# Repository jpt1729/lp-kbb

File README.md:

# Low-profile Keyboard

This is a low profile 65% keyboard with a rotary encoder (for volume + mute/unmute). This project uses Gateron's ks33 switches and their respective hotswap sockets. This is all on top of a skeletal 3d printed case. (also texas themed)

I made this project because 1 I just want a custom keyboard and 2 the keyboard I want kinda doesn't exist. I don't haven't really seen these keyboard with the skeletal cases or chamfered edges so I kinda wanted to make it + its texas themed :).

# Photos

# BOM
| Item | Quantity Used | Quantity Purchased | Designator | Part Number / Description | Link | Cost |
|------|---------------|--------------------|------------|----------------------------|------|------|
| Gateron Grey Heron LP Switches | 70 | 2 (35-pack) | SW1–SW70 | Gateron Low‑Profile Grey Heron | [Gateron](https://www.gateron.com/products/gateron-low-profile-grey-heron-switch?VariantsId=10866) | $30.10 |
| Gateron Sky Plate-Mounted Stabilizer | 1 | 1 | STAB1 | Gateron Low‑Profile Stabilizer | [Gateron](https://www.gateron.com/products/gateron-low-profile-sky-plate-mounted-stabilizer) | $10.00 |
| Gateron Hot‑Swap PCB Socket | 1 | 1 | S1 | LP Hotswap Socket | [Gateron](https://www.gateron.com/products/gateron-low-profile-switch-hot-swap-pcb-socket?VariantsId=10233) | $7.00 |
| Low profile keycaps | 1 | 1 | | Keycaps | [kbdcraft](https://kbdcraft.store/products/keycap-lp) | $20.35 |
| EC11 | 1 | 1 | EC11 | EC11 Encoder |  | *Owned* |
| 1N4148 Diodes | 1 | 1 | D | Keyboard Diodes | [AliExpress](https://www.aliexpress.us/item/2255799955957794.html) | $1.48 |
| Heatset inserts| 1 | 1 |  | | [AliExpress](https://www.aliexpress.us/item/3256807534424119.html) | $2.71 |
| Orpheus Pico | 1 | 1 | U1 | RP2040 Custom Module |  | *Owned* |
| EC11 Encoder | 1 | 1 | ENC2 | EC11 (Spare) |  | *Owned* |
| Headers | 1 | 1 | | 2.54mm Male/Female Headers | [AliExpress](https://www.aliexpress.us/item/2255800687544049.html) | $1.99 |
| PCB (w/o discount) + shipping | 1 | 5 |  | JLCPCB |  | $30.76 |
| Case | 1 | 1 |  | 3d printed case |  | |
| Shipping Gateron (+ Gateron service fee) |  |  |  | Shipping from Gateron |  | $11.23 |
| Shipping AliExpress |  |  |  | Shipping from AliExpress |  | $3.00 |
| **Total** |  |  |  | | | **$118.62** |

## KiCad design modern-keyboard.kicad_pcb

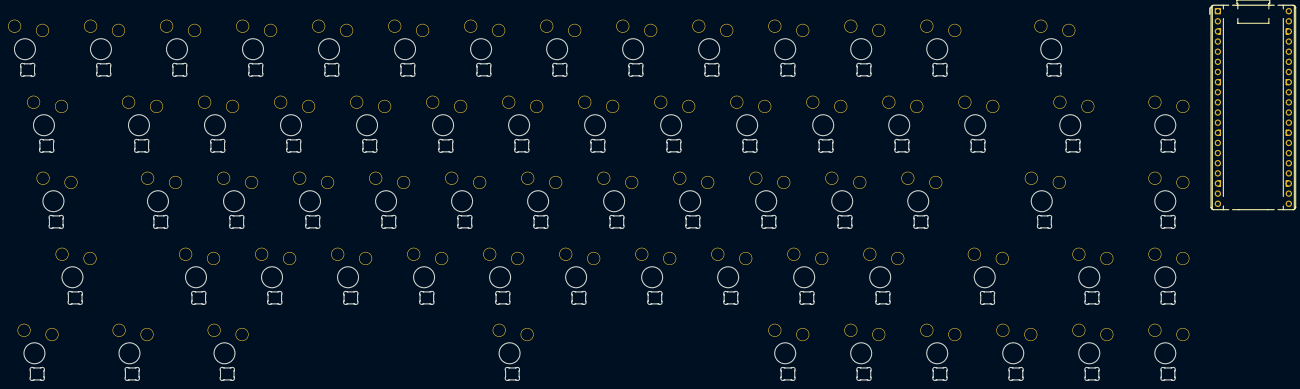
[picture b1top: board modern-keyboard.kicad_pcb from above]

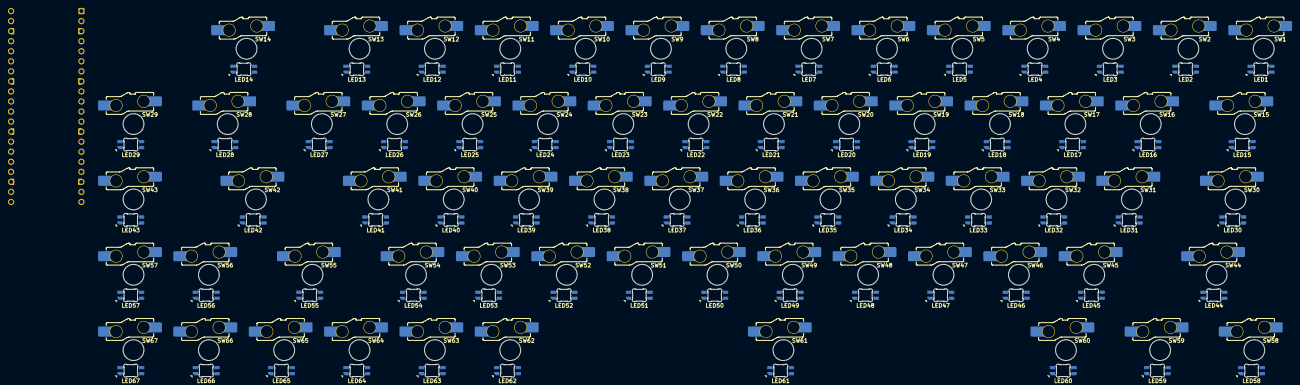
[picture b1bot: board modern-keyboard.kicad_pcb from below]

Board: 2 copper layers, 135 parts (134 on the bottom side), 84 nets, no tracks yet.

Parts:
A1: RaspberryPi_Pico; RaspberryPi_Pico_Common_THT
LED1, LED2, LED3, LED4, LED5, LED6, LED7, LED8, LED9, LED10, LED11, LED12, LED13, LED14, LED15, LED16, LED17, LED18, LED19, LED20, LED21, LED22, LED23, LED24, LED25, LED26, LED27, LED28, LED29, LED30, LED31, LED32, LED33, LED34, LED35, LED36, LED37, LED38, LED39, LED40, LED41, LED42, LED43, LED44, LED45, LED46, LED47, LED48, LED49, LED50, LED51, LED52, LED53, LED54, LED55, LED56, LED57, LED58, LED59, LED60, LED61, LED62, LED63, LED64, LED65, LED66, LED67: SK6812MINI-E; LED_KS33_6028R
SW1, SW2, SW3, SW4, SW5, SW6, SW7, SW8, SW9, SW10, SW11, SW12, SW13, SW16, SW17, SW18, SW19, SW20, SW21, SW22, SW23, SW24, SW25, SW26, SW27, SW29, SW31, SW32, SW33, SW34, SW35, SW36, SW37, SW38, SW39, SW40, SW41, SW43, SW45, SW46, SW47, SW48, SW49, SW50, SW51, SW52, SW53, SW54, SW56, SW57, SW62, SW63, SW64, SW65, SW66, SW67: SW_Push_45deg; SW_KS33_HS_KS-2P02B01-02_HS_1u
SW14: SW_Push_45deg; SW_KS33_HS_KS-2P02B01-02_HS_2u
SW15, SW28: SW_Push_45deg; SW_KS33_HS_KS-2P02B01-02_1.5u
SW30, SW55: SW_Push_45deg; SW_KS33_HS_KS-2P02B01-02_1.75u
SW42, SW44: SW_Push_45deg; SW_KS33_HS_KS-2P02B01-02_HS_2.25u
SW58, SW59, SW60: SW_Push_45deg; SW_KS33_HS_KS-2P02B01-02_1.25u
SW61: SW_Push_45deg; SW_KS33_HS_KS-2P02B01-02_HS_6.25u

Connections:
+5V: A1.40 (VBUS), LED1.1 (VDD), LED2.1 (VDD), LED3.1 (VDD), LED4.1 (VDD), LED5.1 (VDD), LED6.1 (VDD), LED7.1 (VDD), LED8.1 (VDD), LED9.1 (VDD), LED10.1 (VDD), LED11.1 (VDD), LED12.1 (VDD), LED13.1 (VDD), LED14.1 (VDD), LED15.1 (VDD), LED16.1 (VDD), LED17.1 (VDD), LED18.1 (VDD), LED19.1 (VDD), LED20.1 (VDD), LED21.1 (VDD), LED22.1 (VDD), LED23.1 (VDD), LED24.1 (VDD), LED25.1 (VDD), LED26.1 (VDD), LED27.1 (VDD), LED28.1 (VDD), LED29.1 (VDD), LED30.1 (VDD), LED31.1 (VDD), LED32.1 (VDD), LED33.1 (VDD), LED34.1 (VDD), LED35.1 (VDD), LED36.1 (VDD), LED37.1 (VDD), LED38.1 (VDD), LED39.1 (VDD), LED40.1 (VDD), LED41.1 (VDD), LED42.1 (VDD), LED43.1 (VDD), LED44.1 (VDD), LED45.1 (VDD), LED46.1 (VDD), LED47.1 (VDD), LED48.1 (VDD), LED49.1 (VDD), LED50.1 (VDD), LED51.1 (VDD), LED52.1 (VDD), LED53.1 (VDD), LED54.1 (VDD), LED55.1 (VDD), LED56.1 (VDD), LED57.1 (VDD), LED58.1 (VDD), LED59.1 (VDD), LED60.1 (VDD), LED61.1 (VDD), LED62.1 (VDD), LED63.1 (VDD), LED64.1 (VDD), LED65.1 (VDD), LED66.1 (VDD), LED67.1 (VDD)
Col 0: A1.1 (GPIO0), SW1.1, SW15.1, SW30.1, SW44.1, SW57.1
Col 1: A1.2 (GPIO1), SW2.1, SW16.1, SW31.1, SW45.1, SW59.1
Col 2: A1.4 (GPIO2), SW3.1, SW17.1, SW32.1, SW46.1, SW60.1
Col 3: A1.5 (GPIO3), SW4.1, SW18.1, SW33.1, SW47.1
Col 4: A1.6 (GPIO4), SW5.1, SW19.1, SW34.1, SW48.1
Col 5: A1.7 (GPIO5), SW6.1, SW20.1, SW35.1, SW49.1, SW61.1
Col 6: A1.9 (GPIO6), SW7.1, SW21.1, SW36.1, SW50.1
Col 7: A1.10 (GPIO7), SW8.1, SW22.1, SW37.1, SW51.1
Col 8: A1.11 (GPIO8), SW9.1, SW23.1, SW38.1, SW52.1
Col 9: A1.12 (GPIO9), SW10.1, SW24.1, SW39.1, SW53.1, SW62.1
Col 10: A1.14 (GPIO10), SW11.1, SW25.1, SW40.1, SW54.1, SW63.1
Col 11: A1.15 (GPIO11), SW12.1, SW26.1, SW41.1, SW64.1
Col 12: A1.16 (GPIO12), SW13.1, SW27.1, SW55.1, SW65.1
Col 13: A1.17 (GPIO13), SW14.1, SW28.1, SW42.1, SW56.1, SW66.1
Col 14: A1.19 (GPIO14), SW29.1, SW43.1, SW58.1, SW67.1
GND: A1.3 (GND), A1.8 (GND), A1.13 (GND), A1.18 (GND), A1.23 (GND), A1.28 (GND), A1.38 (GND), LED1.4 (VSS), LED2.4 (VSS), LED3.4 (VSS), LED4.4 (VSS), LED5.4 (VSS), LED6.4 (VSS), LED7.4 (VSS), LED8.4 (VSS), LED9.4 (VSS), LED10.4 (VSS), LED11.4 (VSS), LED12.4 (VSS), LED13.4 (VSS), LED14.4 (VSS), LED15.4 (VSS), LED16.4 (VSS), LED17.4 (VSS), LED18.4 (VSS), LED19.4 (VSS), LED20.4 (VSS), LED21.4 (VSS), LED22.4 (VSS), LED23.4 (VSS), LED24.4 (VSS), LED25.4 (VSS), LED26.4 (VSS), LED27.4 (VSS), LED28.4 (VSS), LED29.4 (VSS), LED30.4 (VSS), LED31.4 (VSS), LED32.4 (VSS), LED33.4 (VSS), LED34.4 (VSS), LED35.4 (VSS), LED36.4 (VSS), LED37.4 (VSS), LED38.4 (VSS), LED39.4 (VSS), LED40.4 (VSS), LED41.4 (VSS), LED42.4 (VSS), LED43.4 (VSS), LED44.4 (VSS), LED45.4 (VSS), LED46.4 (VSS), LED47.4 (VSS), LED48.4 (VSS), LED49.4 (VSS), LED50.4 (VSS), LED51.4 (VSS), LED52.4 (VSS), LED53.4 (VSS), LED54.4 (VSS), LED55.4 (VSS), LED56.4 (VSS), LED57.4 (VSS), LED58.4 (VSS), LED59.4 (VSS), LED60.4 (VSS), LED61.4 (VSS), LED62.4 (VSS), LED63.4 (VSS), LED64.4 (VSS), LED65.4 (VSS), LED66.4 (VSS), LED67.4 (VSS)
unnamed: LED1.2 (DOUT), LED2.3 (DIN)
unnamed: LED2.2 (DOUT), LED3.3 (DIN)
unnamed: LED3.2 (DOUT), LED4.3 (DIN)
unnamed: LED4.2 (DOUT), LED5.3 (DIN)
unnamed: LED5.2 (DOUT), LED6.3 (DIN)
unnamed: LED6.2 (DOUT), LED7.3 (DIN)
unnamed: LED7.2 (DOUT), LED8.3 (DIN)
unnamed: LED8.2 (DOUT), LED9.3 (DIN)
unnamed: LED9.2 (DOUT), LED10.3 (DIN)
unnamed: LED10.2 (DOUT), LED11.3 (DIN)
unnamed: LED11.2 (DOUT), LED12.3 (DIN)
unnamed: LED12.2 (DOUT), LED13.3 (DIN)
unnamed: LED13.2 (DOUT), LED14.3 (DIN)
unnamed: LED14.2 (DOUT), LED15.3 (DIN)
unnamed: LED15.2 (DOUT), LED16.3 (DIN)
unnamed: LED16.2 (DOUT), LED17.3 (DIN)
unnamed: LED17.2 (DOUT), LED18.3 (DIN)
unnamed: LED18.2 (DOUT), LED19.3 (DIN)
unnamed: LED19.2 (DOUT), LED20.3 (DIN)
unnamed: LED20.2 (DOUT), LED21.3 (DIN)
unnamed: LED21.2 (DOUT), LED22.3 (DIN)
unnamed: LED22.2 (DOUT), LED23.3 (DIN)
unnamed: LED23.2 (DOUT), LED24.3 (DIN)
unnamed: LED24.2 (DOUT), LED25.3 (DIN)
unnamed: LED25.2 (DOUT), LED26.3 (DIN)
unnamed: LED26.2 (DOUT), LED27.3 (DIN)
unnamed: LED27.2 (DOUT), LED28.3 (DIN)
unnamed: LED28.2 (DOUT), LED29.3 (DIN)
unnamed: LED29.2 (DOUT), LED30.3 (DIN)
unnamed: LED30.2 (DOUT), LED31.3 (DIN)
unnamed: LED31.2 (DOUT), LED32.3 (DIN)
unnamed: LED32.2 (DOUT), LED33.3 (DIN)
unnamed: LED33.2 (DOUT), LED34.3 (DIN)
unnamed: LED34.2 (DOUT), LED35.3 (DIN)
unnamed: LED35.2 (DOUT), LED36.3 (DIN)
unnamed: LED36.2 (DOUT), LED37.3 (DIN)
unnamed: LED37.2 (DOUT), LED38.3 (DIN)
unnamed: LED38.2 (DOUT), LED39.3 (DIN)
unnamed: LED39.2 (DOUT), LED40.3 (DIN)
unnamed: LED40.2 (DOUT), LED41.3 (DIN)
unnamed: LED41.2 (DOUT), LED42.3 (DIN)
unnamed: LED42.2 (DOUT), LED43.3 (DIN)
unnamed: LED43.2 (DOUT), LED44.3 (DIN)
unnamed: LED44.2 (DOUT), LED45.3 (DIN)
unnamed: LED45.2 (DOUT), LED46.3 (DIN)
unnamed: LED46.2 (DOUT), LED47.3 (DIN)
unnamed: LED47.2 (DOUT), LED48.3 (DIN)
unnamed: LED48.2 (DOUT), LED49.3 (DIN)
unnamed: LED49.2 (DOUT), LED50.3 (DIN)
unnamed: LED50.2 (DOUT), LED51.3 (DIN)
unnamed: LED51.2 (DOUT), LED52.3 (DIN)
unnamed: LED52.2 (DOUT), LED53.3 (DIN)
unnamed: LED53.2 (DOUT), LED54.3 (DIN)
unnamed: LED54.2 (DOUT), LED55.3 (DIN)
unnamed: LED55.2 (DOUT), LED56.3 (DIN)
unnamed: LED56.2 (DOUT), LED57.3 (DIN)
unnamed: LED57.2 (DOUT), LED58.3 (DIN)
unnamed: LED58.2 (DOUT), LED59.3 (DIN)
unnamed: LED59.2 (DOUT), LED60.3 (DIN)
unnamed: LED60.2 (DOUT), LED61.3 (DIN)
unnamed: LED61.2 (DOUT), LED62.3 (DIN)
unnamed: LED62.2 (DOUT), LED63.3 (DIN)
unnamed: LED63.2 (DOUT), LED64.3 (DIN)
unnamed: LED64.2 (DOUT), LED65.3 (DIN)
unnamed: LED65.2 (DOUT), LED66.3 (DIN)
unnamed: LED66.2 (DOUT), LED67.3 (DIN)
RGB: A1.20 (GPIO15), LED1.3 (DIN)

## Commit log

2025-07-19 initial PCBs
2025-07-19 correct side correct orientation keyboard + leds
2025-07-24 organization
2025-07-28 final
